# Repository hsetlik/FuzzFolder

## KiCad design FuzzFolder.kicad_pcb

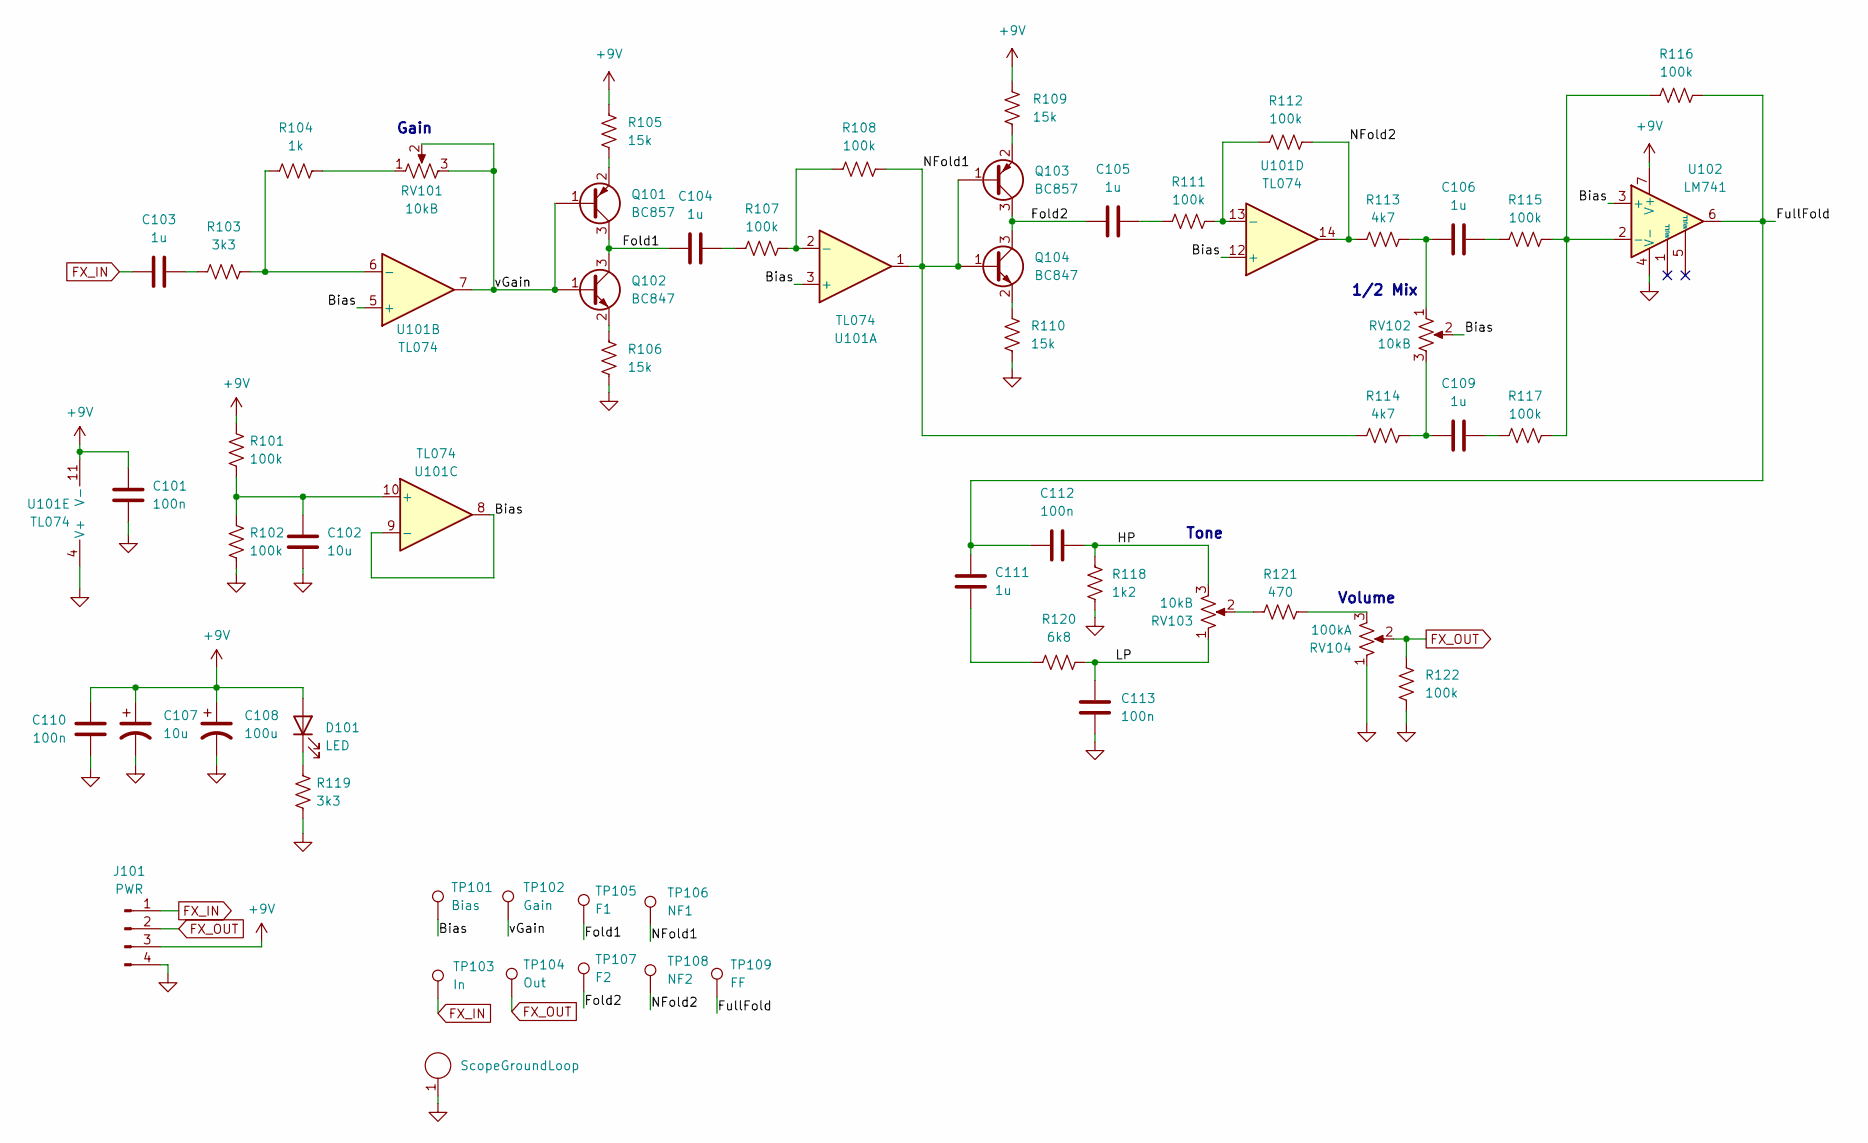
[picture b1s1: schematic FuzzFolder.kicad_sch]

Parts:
C101, C110, C112, C113: 100n; C_0805_2012Metric
C102: 10u; C_0805_2012Metric
C103, C104, C105, C106, C109, C111: 1u; C_0805_2012Metric
C107: 10u; CP_Radial_D5.0mm_P2.50mm
C108: 100u; CP_Radial_D5.0mm_P2.50mm
D101: LED; LED_D3.0mm
J101: PWR; PinHeader_1x04_P2.54mm_Vertical
J102: ScopeGroundLoop; THT_GND_WIRE
Q101, Q103: BC857; SOT-23
Q102, Q104: BC847; SOT-23
R101, R102, R107, R108, R111, R112, R115, R116, R117, R122: 100k; R_0805_2012Metric
R103, R119: 3k3; R_0805_2012Metric
R104: 1k; R_0805_2012Metric
R105, R106, R109, R110: 15k; R_0805_2012Metric
R113, R114: 4k7; R_0805_2012Metric
R118: 1k2; R_0805_2012Metric
R120: 6k8; R_0805_2012Metric
R121: 470; R_0805_2012Metric
RV101, RV102, RV103: 10kB; Potentiometer_Alpha_RV16AF_42_VeryLong
RV104: 100kA; Potentiometer_Alpha_RV16AF_42_VeryLong
TP101: Bias; TestPoint_THTPad_D2.0mm_Drill1.0mm_VAL
TP102: Gain; TestPoint_THTPad_D2.0mm_Drill1.0mm_VAL
TP103: In; TestPoint_THTPad_D2.0mm_Drill1.0mm_VAL
TP104: Out; TestPoint_THTPad_D2.0mm_Drill1.0mm_VAL
TP105: F1; TestPoint_THTPad_D2.0mm_Drill1.0mm_VAL
TP106: NF1; TestPoint_THTPad_D2.0mm_Drill1.0mm_VAL
TP107: F2; TestPoint_THTPad_D2.0mm_Drill1.0mm_VAL
TP108: NF2; TestPoint_THTPad_D2.0mm_Drill1.0mm_VAL
TP109: FF; TestPoint_THTPad_D2.0mm_Drill1.0mm_VAL
U101: TL074; DIP-14_W7.62mm
U102: LM741; DIP-8_W7.62mm

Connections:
+9V: C101.1, C107.1, C108.1, C110.1, D101.2 (A), J101.3, R101.1, R105.1, R109.1, U101.11 (V-), U102.7 (V+)
/Bias: RV102.2, TP101.1, U101.3 (+), U101.5 (+), U101.8, U101.9 (-), U101.12 (+), U102.3 (+)
/Fold1: C104.1, Q101.3 (C), Q102.3 (C), TP105.1
/Fold2: C105.1, Q103.3 (C), Q104.3 (C), TP107.1
/FullFold: C111.1, C112.1, R116.2, TP109.1, U102.6
/HP: C112.2, R118.1, RV103.3
/LP: C113.1, R120.2, RV103.1
/NFold1: Q103.1 (B), Q104.1 (B), R108.2, R114.1, TP106.1, U101.1
/NFold2: R112.2, R113.1, TP108.1, U101.14
/vGain: Q101.1 (B), Q102.1 (B), RV101.2, RV101.3, TP102.1, U101.7
FX_IN: C103.1, J101.1, TP103.1
FX_OUT: J101.2, R122.1, RV104.2, TP104.1
GND: C101.2, C102.2, C107.2, C108.2, C110.2, C113.2, J101.4, J102.1, R102.2, R106.2, R110.2, R118.2, R119.2, R122.2, RV104.1, U101.4 (V+), U102.4 (V-)
unnamed: C103.2, R103.1
unnamed: C104.2, R107.1
unnamed: C105.2, R111.1
unnamed: C106.1, R113.2, RV102.1
unnamed: C106.2, R115.1
unnamed: C109.1, R114.2, RV102.3
unnamed: C109.2, R117.1
unnamed: C111.2, R120.1
unnamed: D101.1 (K), R119.1
unnamed: Q101.2 (E), R105.2
unnamed: Q102.2 (E), R106.1
unnamed: Q103.2 (E), R109.2
unnamed: Q104.2 (E), R110.1
unnamed: R104.2, RV101.1
unnamed: R121.1, RV103.2
unnamed: R121.2, RV104.3
unnamed: R107.2, R108.1, U101.2 (-)
unnamed: R103.2, R104.1, U101.6 (-)
unnamed: C102.1, R101.2, R102.1, U101.10 (+)
unnamed: R111.2, R112.1, U101.13 (-)
unnamed: R115.2, R116.1, R117.2, U102.2 (-)

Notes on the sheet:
Volume
Tone
Gain
1/2 Mix

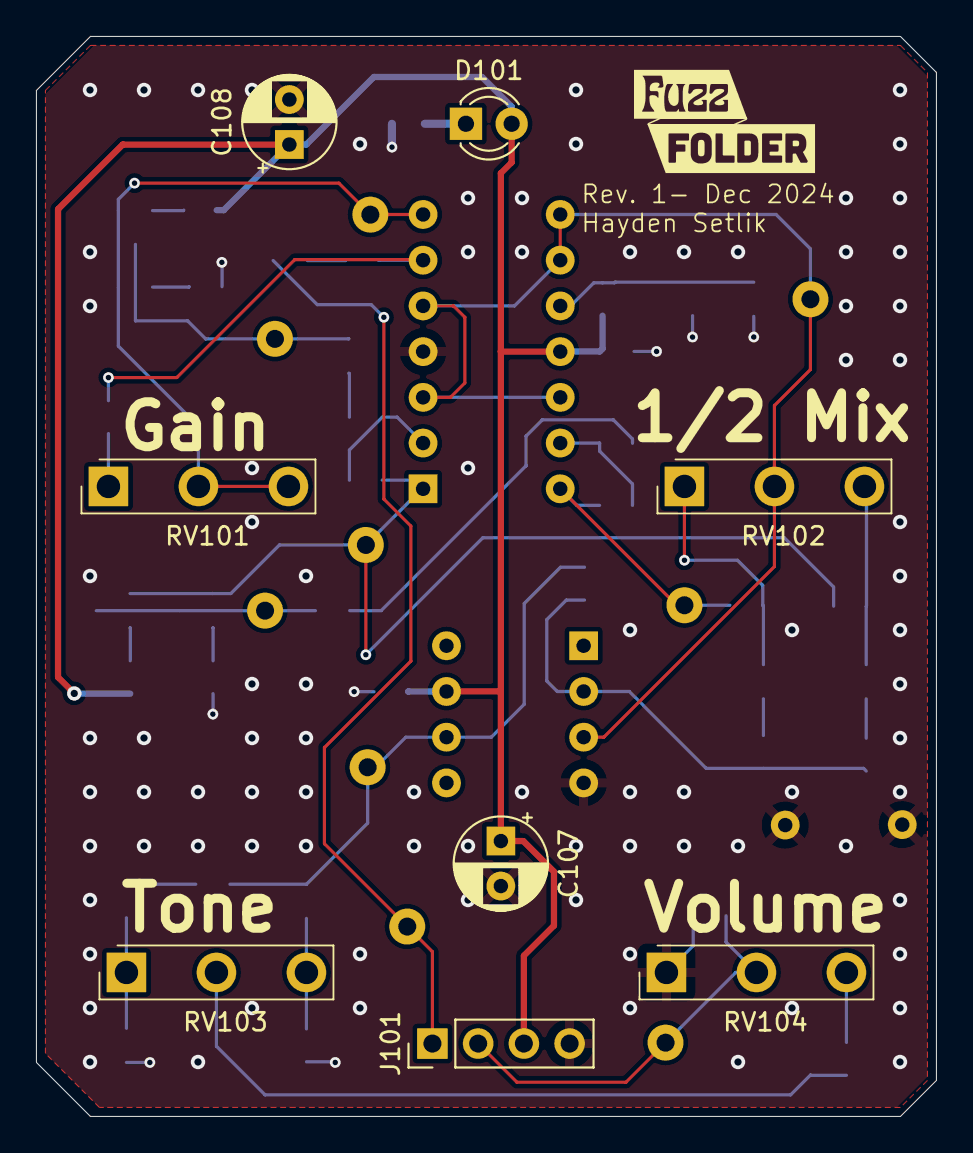
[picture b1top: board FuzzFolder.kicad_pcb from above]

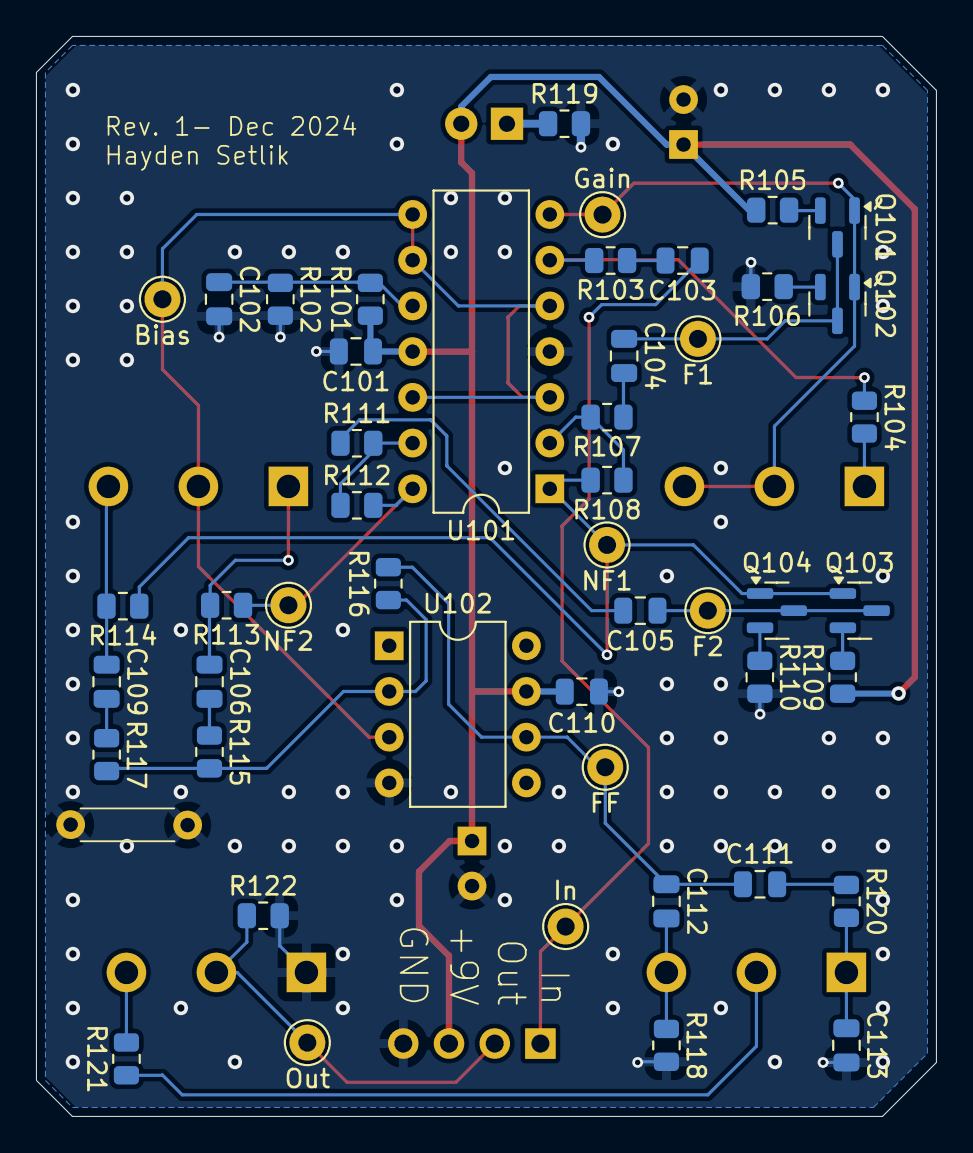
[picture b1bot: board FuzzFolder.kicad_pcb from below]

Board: 4 copper layers, 50.0 x 60.0 mm, 57 parts (49 on the bottom side), 34 nets.

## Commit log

2024-12-20 4layer sent to fab
